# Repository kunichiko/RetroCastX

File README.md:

# RetroCastX

レトロPC(X68000 / PC-98 など)のアナログRGB信号を、フレームバッファレスで PC/Mac に伝送・表示するプロジェクト。

```
Retro PC ──アナログRGB──▶ ADC(TVP7002) ──24bit+PCLK──▶ FPGA(ECP5) ──UDP/GbE──▶ PC/Mac(再構成・表示)
```

## 設計思想

一般的なアップスキャンコンバータは変換器内でフレームバッファを構築し標準的なHDMI信号に整形するため、
機種固有のタイミング情報が失われ、遅延・モード切替時のブラックアウト・価格の問題が生じる。

RetroCastX は「変換器は馬鹿に徹し、知性はPC側に置く」:

- ADC でドットクロックを再生してサンプリングした**生のピクセルデータを、タイミング情報ごと**
  「1パケット≒1ライン」の UDP で送出する(FPGA はラインFIFO程度しか持たない)
- フレームの再構成・スケーリング・表示は PC/Mac 側で行う

これにより:

- **生タイミング保存**: VRR対応モニタなら 55.46Hz(X68000)等の非標準リフレッシュをそのまま表示可能
- **モード切替の無切断追従**: ゲーム中の解像度切替もヘッダ通知で追従
- **真のロスレス**: 8bit で取得し PC 側でパレット吸着(X68000 は本来 RGB 各5bit)
- **低遅延**: サブフレーム(ライン単位)伝送
- **安価**: フレームバッファ用メモリも高度な画像処理も変換器側に不要

## リポジトリ構成

```
docs/
  protocol-v0.md    伝送プロトコル仕様 v0(ドラフト)
  research/         部品・ボード調査レポート
gateware/           FPGA側(LiteX / Colorlight i5)※sim検証済み、実機未検証
hardware/           ADCフロントエンド基板(Atopile、HAT形式)
host/python/        PC側リファレンス実装(送信シミュレータ・受信・検証)
client/             ビューアアプリ(Rust + eframe/egui、Mac/Win/Linux)
client/devsim/      ダミーデバイス(ボードの代役。持っていない機種の信号で Viewer を試す)
```

## クイックスタート(ハードウェア不要)

送信シミュレータと受信器をループバックで動かす:

```sh
cd host/python
python3 -m retrocastx.tests.test_loopback   # プロトコルのE2E検証
python3 -m retrocastx.tests.test_videoin    # コンポジットの波形解析(合成波形で検証)
python3 -m retrocastx.tests.test_ntsc       # NTSC復調(合成6色で真値と照合)
python3 -m retrocastx.sender_sim &          # テストパターンをUDP送出
python3 -m retrocastx.receiver --dump out   # 受信して out/frame_NNNN.ppm に保存
```

## ハードウェア(フェーズ1〜2 想定)

| 役割 | 部品 | 備考 |
|---|---|---|
| FPGAボード | Colorlight i5 + 拡張基板 | ECP5-25F、GbE PHY ×2、SODIMM I/O 直結 |
| ADC | TI TVP7002 | OSSC と同一。15/24/31kHz 実証済み。ブレークアウト自作 |
| 参考回路 | [marqs85/ossc_pcb](https://github.com/marqs85/ossc_pcb) | アナログ入力段・TVP7002 周辺 |

調査の詳細は `docs/research/2026-07-25-hardware-survey.md` を参照。

## ステータス

- [x] 構想・部品調査
- [x] プロトコル v0 ドラフト(映像 LINE/MODE + 音声 AUDIO + 発見/購読 + CONFIG)
- [x] PC側リファレンス実装(シミュレータ + 受信器)
- [x] LiteX ゲートウェア step2(テストパターン送出+購読) — sim検証・ビットストリーム生成済み
- [x] TVP7002 ブレークアウト設計(音声3系統・ArgusX制御含む、電気設計検証まで)
- [x] ビューアアプリ雛形(Rust + eframe、sender_sim相手にE2E確認済み)
- [ ] ゲートウェア実機動作(ボード入手待ち)
- [ ] 基板発注(atopile部品API復旧後にフットプリント紐付け)
- [ ] 音声キャプチャ(gateware step4)・音声再生(client)
- [ ] 実機キャプチャ(X68000 / PC-98)

## ライセンス

ディレクトリごとに異なります。

| 対象 | ライセンス |
|---|---|
| `gateware/` `client/` `host/` | [Apache License 2.0](LICENSE) |
| `hardware/` | [CERN-OHL-S-2.0](hardware/LICENSE)(強い相互性のオープンハードウェアライセンス) |
| `docs/` | [CC BY-SA 4.0](docs/LICENSE) |

`hardware/` の CERN-OHL-S-2.0 は、**この設計を元に製品を作って頒布・販売する場合、
改変を含む設計一式(Complete Source)を公開し、製品または同梱文書に入手先を明記する**
ことを求めます。個人が自分用に作る分にはこの義務は発生しません。

ライセンスの対象外となるファイル(部品メーカーのデータシート、ベンダー由来の
KiCad シンボル・フットプリント等)については [NOTICE](NOTICE) を参照してください。

### 商標

**"RetroCast X"**(正式名称)および **"RetroCastX"**(ファイル名・識別子・
ハッシュタグ等で用いる短縮形)の名称、ロゴ、アイコン、基板シルク上のブランド
表記は、上記いずれのライセンスの許諾範囲にも含まれません
(Apache License 2.0 第6条)。空白の有無・大文字小文字の違いを問いません。

フォークや派生ハードウェアを頒布する場合は、別の名称を用いてください。

### ハードウェアの製造を検討されている方へ

本設計に基づくハードウェアの製造・頒布を計画されている場合、事前にご一報
いただけると嬉しいです。**ライセンス上の義務ではありません**が、既知の問題や
実装上の落とし穴を共有できますし、改善を上流に取り込める場合もあります。

## コントリビューション

歓迎します。手順と DCO(Signed-off-by)については [CONTRIBUTING.md](CONTRIBUTING.md)
を参照してください。特に**手元の実機での動作報告**が助かります。

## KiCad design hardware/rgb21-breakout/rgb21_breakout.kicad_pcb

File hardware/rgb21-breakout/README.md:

# RGB21 → ミニDIN8 変換基板

市販のミニDIN8ケーブルを半分に切り、切った側に **RGB21(JP21)のメスコネクタ**を
付けて、ゲーム機の RGB21 ケーブルを RetroCastX の第2映像入力(J13、FRAMEMEISTER 互換の
ミニDIN8)に挿せるようにする。この基板は RGB21 コネクタのシェル(カバー)の中に収める
三角形の中継基板。

```
ゲーム機 ── RGB21ケーブル(オス) ─┐
                                  ▼
             ┌─ RGB21 メス(J1) ── 基板の端を2列の半田端子で挟む
  シェルの中 │        │ 素通し(部品なし)
             ├─ 芯線パッド(J2) ─ 表4個・裏4個 ─┬ ミニDIN8ケーブル ── RetroCastX J13
             └─ シールドのパッド(J3) ─────────┘
                  └ タイラップ用スロット(H1)でケーブルを基板に縛る
```

回路は**素通しの配線だけ**。分圧・終端・同期分離は入れない。FRAMEMEISTER 付属の
「ミニDIN8→RGB21」ケーブルも素通しで(2026-09-21 に分解して確認)、レベル合わせは
RetroCastX 側(75Ω終端・CSYNC の 1/2 分圧)でやる。

## 結線

| 信号 | RGB21(J1) | ミニDIN8(J2) | J2 の面 |
|---|---|---|---|
| R | 15 | 8 | 裏 |
| G | 19 | 7 | 裏 |
| B | 20 | 6 | 裏 |
| 同期(CSYNC) | 9(コンポジット入力) | 3 | 表 |
| 音声 L | 1 | 2 | 表 |
| 音声 R | 5 | 1 | 表 |
| GND | 3, 4, 7, 8, 13, 14, 17, 18 | 4 | 表 |
| シェル(FG) | 21 | シールド(編組) | J3(スルーホール) |
| 使わない | 2, 6, 10(モニタの出力), 11 AV制御, 12 Ym, 16 Ys | 5(パッドはあるがどこにも繋がない) | 裏 |

- RGB21 のピン名はモニタ(受け側)から見た名前。ゲーム機のケーブルを挿すので、
  ゲーム機の出力は「入力」のピンに来る。出典: ja.wikipedia「RGB21ピン」と
  retrogamingcables の JP21 表(R/G/B/同期/音声で一致)。
- 同期は 9番。RGB21 には同期専用ピンが無く、ゲーム機は CSYNC かコンポジット映像を
  ここに出す。
- ミニDIN8 は FRAMEMEISTER RGB IN と同じ並び(`hardware/adc-frontend` の
  `MiniDin8Rgb` の docstring)。5番は使わないが、芯線の端を留めるためのパッド(どこにも繋がない)がある。
- FG(シェル/シールド)は GND と分けてある。RetroCastX 側で J13 のシェルが GND に
  繋がるので、ケーブルを挿せば同電位になる。
- **J2 はピン番号順に並べてある**: 表が 1 2 3 4(表から見て左→右)、裏が 5 6 7 8 で、
  1 の真裏が 5、2 の真裏が 6 … になる。この基板の目的は芯線を付けやすくすることなので、
  基板上の配線が交差しても番号順を優先した。シルクにはパッドの脇にピン番号、その外に
  信号名を書いてある。表・裏は J2 のフットプリントから見た面で、PCB 上で J2 を裏返して
  置けば入れ替わる。
- **シールド(FG)は J3 に分けた**: より合わせた編組は太く、芯線のパッドと並べると
  隣に触れやすいので、離して置ける別部品のスルーホールパッド(直径 3.5mm・穴 1.8mm)にした。
  表裏どちらからでも付けられ、穴に通せば抜けにくい。
- **芯線の色はケーブルごとに違う。** 半田付けの前に、プラグのピンと芯線の導通を
  テスタで確かめて色を控えること。

## 回路は kinema で書いている

atopile ではなく [kinema](https://github.com/toyoshim-i/kinema) を試している。
Verilog の構造記述のサブセットで部品と接続を書き、KiCad のネットリストを生成する。
**回路図(.kicad_sch)は無い。** 正本は `src/` と `lib/` の `.v`。

| ファイル | 中身 |
|---|---|
| `src/rgb21_breakout.v` | 回路(J1 と J2・J3 の接続) |
| `lib/parts.v` | 部品(ピン番号と電気的な向き) |
| `rgb21_breakout.pretty/` | 自作フットプリント。**`tools/gen_footprints.py` の生成物なので手で直さない** |
| `fp-lib-table` | 上のフットプリントを `rgb21_breakout:` で参照する表 |
| `kinema.toml` | kinema の設定 |
| `rgb21_breakout.kicad_pcb` | 基板。配置・配線はここで手作業 |
| `tools/make_board.py` | PCB を最初の1回だけ作ったスクリプト(PCB があれば何もしない) |

### kinema の入れ方

2026-11-23 時点で GitHub Releases の最新バイナリ(v0.5.0)はソースの版(0.6.4)より
古いので、ソースから入れた(Rust が要る):

```sh
git clone https://github.com/toyoshim-i/kinema
cargo install --path kinema/crates/kinema-cli
```

### 回路を変えたとき

このフォルダで:

```sh
kinema fmt src/*.v lib/*.v           # 正規形に整形(check の fmt 段が要求する)
kinema check --stage lint            # 文法・接続・フットプリントの有無・パッド数
kinema netlist -o build/rgb21_breakout.net
```

そのあと PCB エディタで **File → Import → Netlist…** から `build/rgb21_breakout.net`
を読み込む(**「タイムスタンプで照合」**を選ぶ)。部品の同一性は `.v` の
`(* id = "..." *)` から作られる UUID で決まるので、参照番号を変えても配置は残る。
`id` を変えると別部品扱いになり、配置が消えるので変えないこと。

配線を終えたら照合:

```sh
kinema check --stage equiv           # PCB のパッドとネットが回路と一致するか
```

R と G を入れ替えた PCB で `net-partition-mismatch` が出ることを確かめてある。

### kinema 0.6.4 で踏んだこと

- **`fp-lib-table` を相対パスで指定すると自作フットプリントが見つからない。**
  表の置き場所を `${KIPRJMOD}` にするとき親ディレクトリが空文字になり、
  `/rgb21_breakout.pretty` を探しに行って `footprint-missing` になる。自動検出でも
  同じ。`kinema.toml` で `fp_lib_table = "./fp-lib-table"` と `./` 付きで書いて回避した。
- 全ピンを `passive` にすると全ネットに `undriven-net` の警告が出る。J1 の使う信号は
  `output`、J2 の信号は `input`、J2 の GND/シールドは `power_out` にしてある。
- **`check --stage equiv` は、どこにも繋がないパッドが PCB に無くても通る。** ネットのある
  パッドしか比べないため。J2 に5番(NC)のパッドを足したとき、古いフットプリントのままの
  PCB でも照合が通った。パッドの数は `--stage lint` がライブラリ側でしか見ないので、
  フットプリントを変えたら PCB 側の更新は目で確かめる。
- タイラップのスロット(H1)は回路に無い部品なので、フットプリントに
  `(attr board_only)` を付けて照合から外している。

## 残りの作業

1. **寸法を実測して `tools/gen_footprints.py` の ★ の値を直す**:
   - ~~RGB21 端子のピッチ~~ → SCART の仕様で同じ列 3.81mm(列どうしは半ピッチ 1.905mm ずれて
     交互に並ぶ)に決めた。全幅はピン1〜21の中心で 38.1mm
   - 端子の板幅と基板に乗る長さ(パッド 2.0 × 4.0mm で仮置き)
   - 2列の間隔が基板の厚み(1.6mm)で挟めるか。合わなければ板厚を変える(1.2 / 2.0mm など)
   - どちらの列が奇数ピン(1〜19 と 21=シェル)か。今は奇数を裏、偶数を表にしてある
   - タイラップの幅・厚みとケーブルの外径(スロット 1.3 × 3.2mm、中心間 9mm)
   - より合わせたシールドの太さ(J3 の穴 1.8mm、パッド 3.5mm)

   直したら `python3 tools/gen_footprints.py` を実行し、PCB エディタで
   Tools → Update Footprints from Library。
2. **外形と配線は一通り済んだ**(2026-11-24、DRC 違反 0・未配線 0、`kinema check --stage equiv` 通過)。
   ただし上の ★ の寸法は仮置きのままなので、実測で値が変わったら外形・配置・配線を見直す。
   外形はシェル内の三角形に合わせ、J1 の原点(Fab 層の破線 "board edge")が差し込む辺。

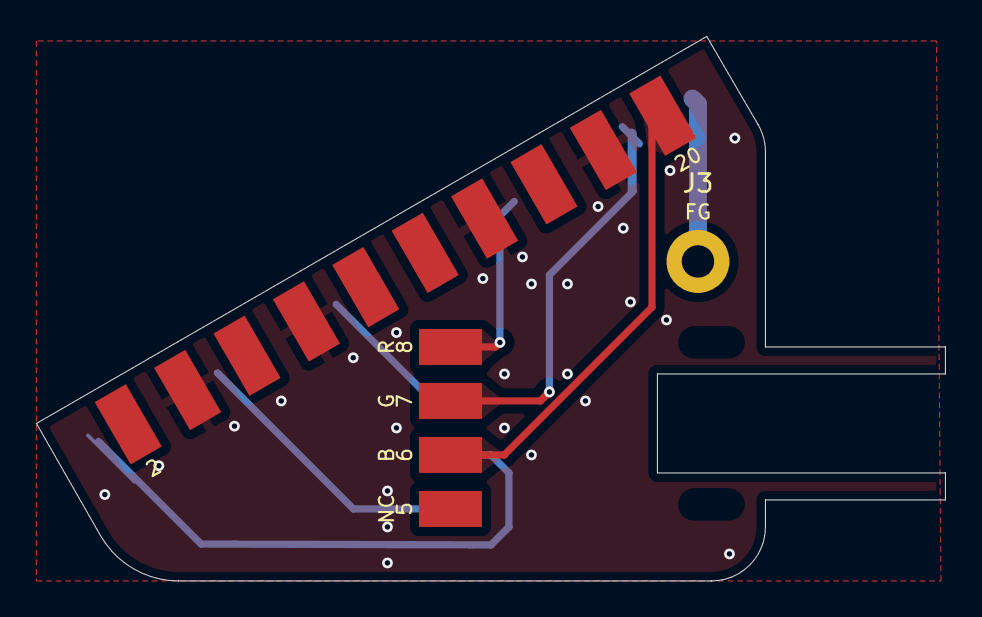
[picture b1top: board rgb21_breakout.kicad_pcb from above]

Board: 2 copper layers, 50.5 x 30.2 mm, 4 parts (1 on the bottom side), 8 nets.

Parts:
H1: CableTie_Slots
J1: RGB21_Female; RGB21_CardEdge
J2: MiniDin8_Cable; MiniDin8_WirePads
J3: ShieldWirePad; FG_WirePad

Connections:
AUDIO_L: J1.1, J2.2
AUDIO_R: J1.5, J2.1
B: J1.20, J2.6
CSYNC: J1.9, J2.3
FG: J1.21, J3.1
G: J1.19, J2.7
GND: J1.3, J1.4, J1.7, J1.8, J1.13, J1.14, J1.17, J1.18, J2.4
R: J1.15, J2.8

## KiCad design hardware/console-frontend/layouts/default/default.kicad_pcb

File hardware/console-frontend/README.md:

# RetroCastX 小亀基板(コンソール入力基板) v1.0

家庭用ゲーム機向けの入力端子を引き受けて、**0.5mmピッチ20芯FFC(10cm)**で
メイン基板(`hardware/adc-frontend`)へ渡すサブ基板。外形はメイン基板と同じ
**10cm × 10cm**、取付穴は M3 ×5(メイン基板の H1-H5 と同じ位置にしてスペーサで重ねられる)。

> **発注済みの v1.0.1 には手作業の改修が2つ要る**(映像の結合コンデンサ C6〜C9 と、
> 音声の分圧)。図つきの手順は [docs/rework-v1.0.1.md](docs/rework-v1.0.1.md)。

```
  S端子(ミニDIN4) ─┬─ESD─ 75Ω ─ 10µ ──┬(bias 1.65V)─┐
                   │                                  ├ SPDT ch1 ─ FFC 9 ─→ GIN_1 / SOGIN_1
  コンポジット(黄) ─┴─ESD─ 75Ω ─ 10µ ──┘              │   (ESD: D2=CVBS/音声L/R
                                                       (選択 = FFC 15 = FPGA GPIO)
  S端子C ───────────ESD─ 75Ω ─ 10µ ───┬──────────────┤    D3=S端子Y/C・Pr/Pb)
  コンポーネントPr(赤)─ESD─ 75Ω ─ 10µ ─┘              └ SPDT ch2 ─ FFC 7 ─→ RIN_1

  コンポーネントPb(青)─ESD────────────────────────────── FFC 5 ─→ BIN_1(終端はメイン基板側)
  音声L(灰/黒) ─ESD─ 10k ─┬─────────────────────────  FFC 1 ─→ PCM1808 #3
                          10k→GND(×0.46。PCM1808 のフルスケール 3Vpp に 2Vrms を収める)
  音声R(赤)   ─ESD─ 10k ─┬─────────────────────────  FFC 3 ─→ PCM1808 #3
                          10k→GND
  シリアルLED ×4 ←── FFC 11(データ)/ 17・18(+3.3V 直結)
```

Y/C分離も復調もこの基板ではやらない。メイン基板の TVP7002 で 8fsc サンプリング
して、Viewer(PC側)でデコードする(`docs/composite-video-plan.md`)。

## 音声のハムはケーブルで決まる(この基板では対処しない)

PS2 のサードパーティ製コンポーネントケーブルで、音声に **59.94Hz とその倍音のハム**
(−58dBFS)が乗った(2026-11-08)。Y を抜くと消え、白い画面ほど大きい。
映像の 75Ω 終端の電流はケーブルの GND を通ってゲーム機へ戻るので、その電圧降下が
ゲーム機と小亀基板の GND の間にでき、ゲーム機の GND 基準で出ている音声に乗る。

テスターで測ると、このケーブルは映像(緑)と音声の GND が **RCA 側の近くで合流し、
マルチ端子まで約1.75Ωを共用**していた(緑⇔ピン 2Ω、音声⇔ピン 2Ω、緑⇔音声 0.5Ω)。
共用区間の電圧降下は受け側で差動にしても消せないので、差動アンプ案は採らなかった。
純正のコンポジット(GND 間 5Ω)/S端子(絶縁)ケーブルではノイズは出ない。
**対策はケーブルを替えること。**

(メイン基板と共通)

メイン基板(J15)側の番号で書く。**小亀基板(J1)は逆順(n ↔ 21-n)**。

| pin | 信号 | pin | 信号 |
|---|---|---|---|
| 1 | 音声L | 11 | LED_DATA |
| 2 | GND | 12 | GND |
| 3 | 音声R | 13 | GPIO2(予備) |
| 4 | GND | 14 | GND |
| 5 | Pb(スイッチを通らない) | 15 | GPIO1(スイッチ選択) |
| 6 | GND | 16 | GND |
| 7 | C / Pr(スイッチ出口) | 17 | +3.3V |
| 8 | GND | 18 | +3.3V |
| 9 | Y / CVBS(スイッチ出口) | 19 | +5V |
| 10 | GND | 20 | +5V |

**信号は全部が両隣にGNDを持ち、電源は2本ずつ**(2026-09-22 に16芯から20芯へ)。
16芯のときは制御3本(LED_DATA/GPIO2/GPIO1)が並んでいて、800kHzのLEDデータが
隣のGPIOと並走していた。電源を2本にしたのは往復抵抗を半分にするため。

★**ケーブルの向き(type A / type D)は発注前に確認すること。** FFCは両端の接点が
同じ面か反対面かで「n番 ↔ n番」と「n番 ↔ 21-n番」が入れ替わる。**このネットリストは
type A(同面接点)+ 2枚を同一平面・開口部を向かい合わせ、を前提に小亀側を
逆順(n ↔ 21-n)で定義してある**(`main.ato` の `FfcMain20` docstring が正典)。
2枚の基板の向きを決めたら紙に描いて種別を選び、**通電前にテスターで
pin1↔pin1 を当たること**。1ピンずれると +5V が GPIO に当たる。

## 入力の切り替え(TS5A23159 / 1本の選択線)

真理値表(データシート SCDS201H Table 2: IN=L → NC-COM が ON)。

| GPIO1 (= FFC 15) | FFC 9 (→GIN_1/SOGIN_1) | FFC 7 (→RIN_1) | FFC 5 (→BIN_1) | 使える入力 |
|---|---|---|---|---|
| **L(既定・10kプルダウン)** | CVBS(黄) | Pr(赤) | Pb(青) | コンポジット / **YPbPrコンポーネント** |
| H | S端子 Y | S端子 C | (Pb) | S端子 |

- **既定をコンポジットにした理由**: ゲートウェアがこのGPIOを駆動しない状態でも
  「黄色いケーブルを挿しただけで映る」ようにするため。S端子とコンポーネントは
  Viewer で明示的に選ぶ操作を伴うので、そのときに H へ駆動される。
- **同期(SOGIN_1)はスイッチの出口から分岐している**ので、映像と同期が必ず
  一緒に切り替わる。人が触る物理スイッチだと「設定はコンポジットなのにスイッチは
  S端子側」という食い違いを作れてしまう(`docs/TODO.md` 10-5)。
- break-before-make なので、切り替えの瞬間に2つのソースが繋がることはない。

## 75Ω終端と中点バイアス(この基板の設計の要点)

**終端はこの基板のジャック側に置く**。メイン基板の `VideoInputChannel` が持つ
75Ω(`r_term`)は、**この基板で終端するチャンネル(Y/C)では実装しない**。
両方に入れると合計37.5Ωになり振幅が半分になる。

終端の直後に 10µF で直流を切り、10kΩ で 1.65V(VCC/2)へ持ち上げてから
スイッチに入れている。理由は**スイッチの信号範囲が GND〜VCC** だから:

★**結合は 10µF(時定数 0.1 秒)。v1.0 初版は 100nF(1ms)だった。** 1ms でも
1ライン(63.5µs)より十分長いつもりだったが、明るい区間の後ろで黒が 7〜9 コード
沈んだ(コンポーネントで実測、2026-11-08。手持ちの 0603 10µF に張り替えて解消)。
S端子の C(C8)は低域を持たないので 100nF でも困らないが、部品を揃えて 4つとも 10µF にした。
同じ理由でメイン基板の SOG 結合(C51)は 1nF にしてある(データシートの指定どおり)。
```
出力にコンデンサが入っている機種(AC結合)を 75Ω でGNDへ終端すると、
波形の平均が0Vになるので同期先端が負に潜る
    暗い絵(平均0.35V)  同期先端 ≈ -0.35V
    白い絵(平均0.85V)  同期先端 ≈ -0.85V   ← 絶対最大 -0.5V を超える
潜る量が絵の明るさで動くので、スイッチの保護ダイオードが同期先端だけを食う。
同期先端は SOG スライサが見ている場所なので、明るい絵のときだけ同期が乱れる。
```

v0.9.0(2x4ヘッダ)は同じ 75Ω→100nF の並びだったが、終端ノードに能動素子が
無かったので問題にならなかった。スイッチを入れる v1.0 では効いてくる。

Pb だけはスイッチを通らないので直流結合のまま渡し、終端もメイン基板側
(`ch_b1` の 75Ω)に任せている。

## 部品(LCSC)

| 部品 | 型番 | LCSC | 備考 |
|---|---|---|---|
| ミニDIN4(S端子) | **マル信 MJ-373/4B** | — (手実装) | 千石/マルツ/モモハラ。3=Y / 4=C / 1,2=GND / スロット3本=シェル |
| RCA ×5 | **RCA-105**(色違い) | — (手実装) | AliExpress等。黄/白/赤/黒/青が同寸法で揃う。**2端子・両方とも軸線上** |
| FFCコネクタ | HDGC 0.5K-1.5-**20**PWB | C2919559 | 下接点・フリップロック・右アングル |
| アナログスイッチ | TI TS5A23159DGSR | C42751 | 2ch SPDT, Ron 1Ω, break-before-make |
| ESD ×2 | onsemi NZQA6V8AXV5T1G | C895163 | メイン基板と同じ。旧 EMZT6.8ET2R(C510333)が JLC 在庫切れのため v1.0 発注前に差し替え。ピン互換(SOT-553 = EMD5 同寸、リード2が共通アノード)で、フットプリントは旧品の5パッド版をそのまま使う |
| シリアルLED ×4 | Worldsemi WS2812B-2020-V6 | C52917434 | 3.3V直結、LED1→LED4 の直列(v1.0 発注前に2個から4個へ)。**MSL 5a(JLCの焼成料金がかかる)**。D1(旧 1N4148W)は欠番 |

ミニDIN4はLCSCに無いので**フットプリントをメーカー図面から自作**した
(`parts/_mech/MJ373_4B.kicad_mod`。φ1.2×4 + スロット2.8×0.8×3、原点=嵌合面)。
メイン基板のミニDIN8(マル信 MJ-373/8B)と同じハウジング/ランド枠。

RCAは**フットプリントをメーカー図面から自作**した(`parts/_mech/RCA105.kicad_mod`)。
ランドは **2端子だけで、両方ともコネクタの軸線上**:

    pad1  スロット 軸方向 1.50 × 横 2.30  @ 嵌合面から 4.80  → シェル(GND)
    pad2  スロット 軸方向 2.30 × 横 1.00  @ 嵌合面から 8.30  → 中心導体(信号)

図面の「2.30x1.50」「1.00x2.30」は軸が縦の図での横×縦。v1.0.0 は軸方向と読み違えて
両スロットが 90° 回っていた(v1.0.1 で修正。pad1 の前足は軸と直角の板、pad2 の後ろ足は軸方向の板)。

★**極性は現物で導通確認すること。** 2端子しかないので取り違えると映像をGNDへ短絡する
(「筒の外側 ↔ pad1」「中心の穴 ↔ pad2」を当てれば10秒)。
★**同じ RCA-105 でも出品元で寸法が違うことがある**ので、4.80/8.30 とスロット寸法を実測してから発注する。
★外形と並べ方(枠10.0mm・筒がφ8.3で9.3mm張り出す・ピッチは12.5mm)は
`docs/layout-guidelines.md` の1章にまとめた。

レイアウトの指示は `docs/layout-guidelines.md`(外形・コネクタ形状・配置・配線ルール)。

## ビルド

```
ato build                               # ネットリスト/PCB/BOM を生成
```

部品の取り込み(atopileの部品APIが落ちているときのオフライン手順)は
メイン基板と同じ `tools/ingest_parts.py`:

```
~/.local/share/uv/tools/atopile/bin/python tools/ingest_parts.py C2939342 ...
```

★**ESDアレイのフットプリント(ROHM_EMZT6_8ET2R。現行の NZQA6V8AXV5T1G もこれを使う)を取り込み直したら `tools/fix_esd_land.py` を必ず走らせる**
(取り込み時のフットプリントはリードの無い裸パッドを含む6パッド版で、パッド幅も
0.28mmしかない)。いまリポジトリに入っているのはメイン基板で修正した5パッド版。

## 発注前チェックリスト

1. **FFCの向き**: type A(同面接点)+ 対向配置の前提で小亀側を逆順(n↔21-n)にしてある。
   紙に描いて確認し、通電前に pin1↔pin1 を導通確認
2. **ミニDIN4のピン**: 現物で「3番がプラグの輝度ピン」を導通確認(図面の
   PCB穴図のパッド番号=ミニDIN4の標準ピン番号として扱っている)
3. **RCA-105 の極性とランド**: pad1=GND / pad2=信号 を導通確認し、4.80/8.30 を実測
4. **メイン基板側の 75Ω**: `ch_y` / `ch_c` の `r_term` を実装しない指定になっているか
   (v1.0 の main.ato では `VideoInputChannelNoTerm` を使う。未対応なら手で外す)
5. 取付穴の位置をメイン基板と合わせる(M3 ×4)

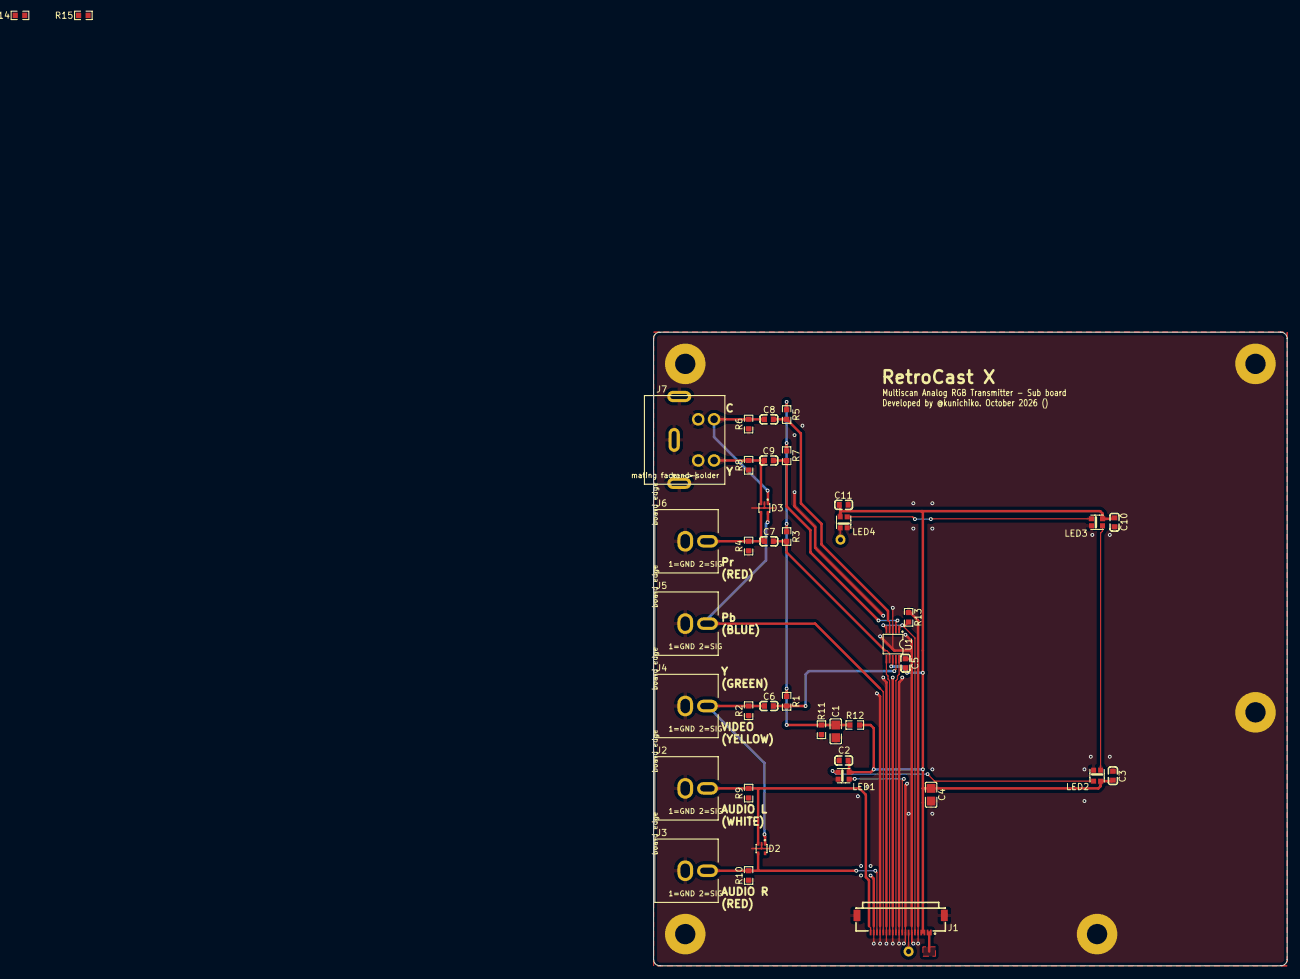
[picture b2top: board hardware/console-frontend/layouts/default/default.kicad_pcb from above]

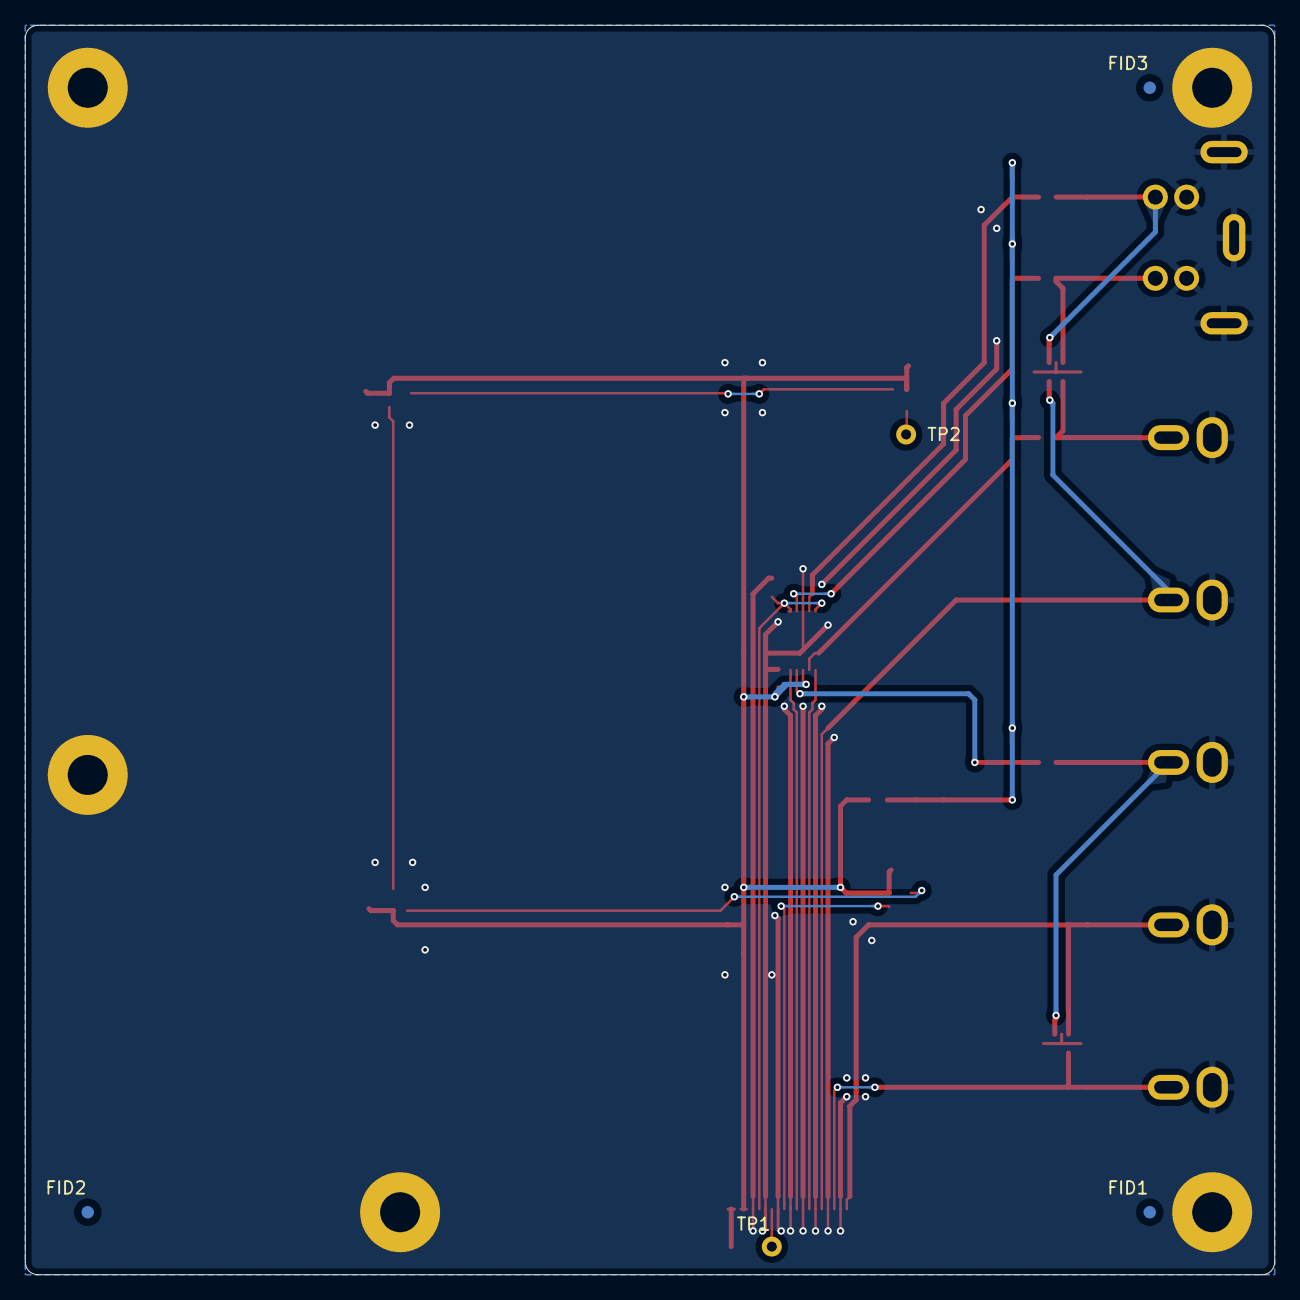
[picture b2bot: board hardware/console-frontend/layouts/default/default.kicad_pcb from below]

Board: 2 copper layers, 100.0 x 100.0 mm, 50 parts (9 on the bottom side), 26 nets.

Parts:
C1, C4: 10µF ±10%; C0805
C2, C3, C5, C10, C11: 100nF ±10%; C0603
C6, C7, C8, C9: 10µF ±10%; C0603
D2, D3: EMT6_L1.6-W1.2-P0.50-LS1.6-BL
FID1, FID2, FID3: Fiducial_1mm_Mask2mm
H1, H2, H3, H4, H5: MountingHole_3.2mm_M3_Pad
J1: FPC-SMD_20P-P0.50_HDGC_0.5K-1.5-20PWB
J2, J3, J4, J5, J6: RCA105
J7: MJ373_4B
LED1, LED2, LED3, LED4: LED-SMD_4P-L2.2-W2.0-P1.00_WS2815C-2020-4P
R1, R3, R5, R7, R9, R10, R11, R12, R13, R14, R15: 10kΩ ±1%; R0603
R2, R4, R6, R8: 75Ω ±1%; R0603
TP1, TP2: TestPoint_TH1
U1: VSSOP-10_L3.0-W3.0-P0.50-LS4.9-BL

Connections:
aud_l_in: D2.3, J2.2, R14.1
aud_l_out: J1.20, R9.1, R14.2
aud_r_in: D2.4, J3.2, R15.1
aud_r_out: J1.18, R10.1, R15.2
c_out: J1.14, U1.6
cvbs_ac: C6.2, R1.1, U1.9
cvbs_in: C6.1, D2.1, J4.2, R2.1
gnd: C1.2, C2.2, C3.2, C4.2, C5.2, C10.2, C11.2, D2.2, D3.2, H1.1, H2.1, H3.1, H4.1, H5.1, J1.5, J1.7, J1.9, J1.11, J1.13, J1.15, J1.17, J1.19, J1.21, J1.22, J2.1, J3.1, J4.1, J5.1, J6.1, J7.1, J7.2, J7.5, J7.6, J7.7, LED1.2, LED2.2, LED3.2, LED4.2, R2.2, R4.2, R6.2, R8.2, R9.2, R10.2, R11.2, R13.2, U1.3
gpio2: J1.8, TP1.1
led1_dout: LED1.1, LED2.3
led2_dout: LED2.1, LED3.3
led3_dout: LED3.1, LED4.3
led4_dout: LED4.1, TP2.1
led_din: J1.10, LED1.3
p3v3: C2.1, C3.1, C4.1, C5.1, C10.1, C11.1, J1.3, J1.4, LED1.4, LED2.4, LED3.4, LED4.4, R12.1, U1.8
p5v: J1.1, J1.2
pb_out: D3.5, J1.16, J5.2
pr_ac: C7.2, R3.1, U1.7
pr_in: C7.1, D3.4, J6.2, R4.1
sv_c_ac: C8.2, R5.1, U1.4
sv_c_in: C8.1, D3.1, J7.4, R6.1
sv_y_ac: C9.2, R7.1, U1.2
sv_y_in: C9.1, D3.3, J7.3, R8.1
sw_sel: J1.6, R13.1, U1.1, U1.5
vbias_1v65: C1.1, R1.2, R3.2, R5.2, R7.2, R11.1, R12.2
y_out: J1.12, U1.10

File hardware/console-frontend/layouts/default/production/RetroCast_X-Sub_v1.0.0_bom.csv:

Designator,Footprint,Quantity,Value,LCSC Part #
"C1, C4",C0805,2,10µF ±10%,C15850
"C10, C11, C2, C3, C5, C6, C7, C8, C9",C0603,9,100nF ±10%,C14663
"D2, D3",EMT6_L1.6-W1.2-P0.50-LS1.6-BL,2,,C895163
J1,FPC-SMD_20P-P0.50_HDGC_0.5K-1.5-20PWB,1,,C2919559
"J2, J3, J4, J5, J6",RCA105,5,,
J7,MJ373_4B,1,,
"LED1, LED2, LED3, LED4",LED-SMD_4P-L2.2-W2.0-P1.00_WS2815C-2020-4P,4,,C52917434
"R1, R10, R11, R12, R13, R3, R5, R7, R9",R0603,9,10kΩ ±1%,C25804
"R2, R4, R6, R8",R0603,4,75Ω ±1%,C4275
"TP1, TP2",TestPoint_TH1,2,,
U1,VSSOP-10_L3.0-W3.0-P0.50-LS4.9-BL,1,,C42751

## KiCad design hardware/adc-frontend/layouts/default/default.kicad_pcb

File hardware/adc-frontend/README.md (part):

# RetroCastX ADC フロントエンド(TVP7002 ブレークアウト)

レトロPCのアナログRGB(VGA HD-15経由)を TI TVP7002 でデジタル化し、
24bitパラレル + DATACLK/HSOUT/VSOUT/SOGOUT を Colorlight i5 EXTボードへ渡す
**HAT基板**(EXTのP1/P2/P4に直接スタック)。GbE MagJack・**音声入力4系統**・
ArgusX制御コネクタ搭載。回路は `main.ato`(Atopile)。

## v1.0 の変更点(v0.9.0 → v1.0)

v0.9.0(2026-08-19 発注、実機動作確認済み)からの差分。**電気的に効く変更**と
**部品・コネクタの入れ替え**を分けて書く。

### 入力コネクタ

| 端子 | v0.9.0 | v1.0 |
|---|---|---|
| アナログRGB | D-SUB15(2列DA-15, X68000式) | 変更なし |
| 第2映像入力 | J4: 2×5 ボックスヘッダ(要自作ケーブル) | **J13: ミニDIN8(FRAMEMEISTER互換)** |
| 第2入力のTTL同期 | 同ヘッダの9/10ピン | **J14: 1×3 ヘッダ(HSYNC/VSYNC/GND)** |
| S端子/コンポジット | J5: 2×4 ボックスヘッダ | **J15: 20芯FFC → 小亀基板**(`hardware/console-frontend`)。並びは `音声L/GND/音声R/GND/Pb/GND/C/GND/Y/GND/LED/GND/GPIO2/GND/GPIO1/GND/+3.3V/+3.3V/+5V/+5V`(全信号がGNDに隣接、電源は2本ずつ) |
| 光デジタル(S/PDIF) | J8: PLR135/**T** | J8: PLR135/**T10**(ランドが小さい) |
| デジタルRGB | J6: 1.25mm 単列8極(SMD) | **J6: 2×5 ボックスヘッダ(ストレート)**(XFCN BH254V-10P, C492442)。一般的な10芯フラットケーブルが使える。位置も別エッジへ移動 |
| USB-C | J2 | 変更なし |

### 電気的な変更

- **同期入力にプルアップ 10kΩ を追加**(R47-R50)。D-SUB と 1x3 ヘッダの
  HSYNC/VSYNC。未接続時にシュミット入力が浮いて自己発振し、捕捉側の `raw_ok` が
  誤って立つ不具合(`docs/TODO.md` 10-5b、実機 2026-09-06)の根本対策。
  **プルダウンではなくプルアップ**(レトロ機のTTL同期は負極性=アイドルHigh。
  オープンコレクタ出力の機種にも対応できる)
- **PCM1808 を2個 → 3個**。映像系統ごとに独立させ、受動加算の 1.5kΩ×4 を廃止
- **BIN_1 を実入力に昇格**(小亀基板の Pb / 予備線)。未使用終端の 10nF を撤去し、
  他のチャンネルと同じ前段(75Ω/100nF/220Ω/33pF)を付けた
- **S/PDIF受信の電源にフェライト+10µFを追加**(FB4/C96)。データシートの応用回路が
  47µH+0.1µF を要求しているのに v0.9.0 は 0.1µF だけだった
- **ネジ穴 M2.6 → M3**(穴2.8→3.2mm、パッド5.6→6.4mm)。ねじとスペーサの入手性
- ミニDIN8 の R/G/B/CSYNC に ESD を追加(v0.9.0 の 2x5 ヘッダ経路には無かった)
- **JTAGデバッグ端子(J3, 1×6ヘッダ)を削除**。「外部JTAG器を繋げるように」という保険
  だったが、**FPGAのJTAGへ届く経路はモジュール底面のパッド = ポゴピンしか無い**ので、
  ポゴピンが届かない場合の保険にはならない(CH347Fが壊れた場合にしか効かない)。
  J3 は欠番のまま(`tools/lock_designators.py` が番号の再利用を防ぐ)
- **ステータスLED(LED1)を WS2812B-2020-V6(C52917434)の 3.3V 直結に変更**。
  V6 は VDD 3.3〜5.3V・VIH 0.55×VDD なので、5V + 1N4148W の降圧が不要になった
  (D7 は欠番)。**MSL 5a のため JLCPCB の焼成料金がかかる**(承知のうえで採用)
- **ESDアレイを onsemi NZQA6V8AXV5T1G(C895163)に差し替え**。EMZT6.8ET2R(C510333)が
  JLCPCB で在庫 0 になったため。SOT-553 は EMD5 と同寸でリード番号も同じ(リード2 = 共通
  アノード)なので、**フットプリントと配線はそのまま**。VBR は同じ 6.47〜7.14V、Ct は
  7pF → 12pF typ に増えるが、映像(37.5Ω 系で極 約350MHz)にも TTL にも実害は無い
- **TVP7002 を PZPR(C527698、テープ&リール品)に変更**。中身とフットプリントは PZP と同じ
- **MAC EEPROM を SOT-23-6 の 24AA025E48T-I/OT(C129895)に変更**。SOIC 版は JLC 在庫が
  足りなかった(-I/SN 6個 / -E/SN 32個、1枚に2個使う)。A2 と WP のピンが無いが、A2 は内部で 0、
  WP は元々 GND 固定(書込み許可)なので 0x50 / 0x51 の割当も動作も同じ
- **手ハンダ部品(J7-J10, J13, J14, PG1-PG4, TP1, TP2)を BOM から除外**(フットプリントに
  exclude_from_bom)。JLC の BOM で「型番なし」の警告が出ないようにするため
- **SOG シャントの未実装 33pF(C32/C40/C52)を 0402 → 0603 に変更**。必要になったら手ハンダで
  載せるため。専用フットプリント `parts/_mech/C0603_DNP`(DNP・BOM/座標ファイル除外)にした。
  0402 版は BOM に型番なしで残り、JLCPCB が勝手に C162097 を割り当てていた

### ソフト側に必要な追随(v1.0 基板を使うとき)

- 音声ソースが3系統になる(`i2s_dout_dsub` / `i2s_dout_din8` / `i2s_dout_kokame`、
  DOUT は SO-DIMM 141 / 139 / **129**)。AUDIOパケットの source 番号が増える
  → **対応済み**: source 0=D-SUB15(U13) / 1=ミニDIN8(U14) / 2=S/PDIF /
  3=小亀基板(U17)。S/PDIF の 2 を動かさず末尾に足した(`docs/protocol-v0.md`)
- 小亀基板のアナログスイッチ選択線が **SO-DIMM 148(K4)**、予備が150(K5)、
  小亀のシリアルLEDデータが **154(A2)**。プロファイルから駆動する
- ミニDIN8 のプロファイルは **SOGスライス閾値(CONFIG key 0x50)を下げる**
  (規格準拠ケーブルのCSYNCは0.3Vpp → 1/2分圧後0.15Vpp。既定のNTH=11=124mVでは
  振幅の83%を切ってしまう。NTH=7 = 79mV が50%点)

## 次の版への要望: 入力ごとの信号検出(2026-11-09)

Viewer は入力を「端子 × 機種」で選ぶ形になり、端子ボタンに信号の有無を出している。
**選んでいない端子の有無も分かるようにしたい**(電源を入れた機械の端子が光る、
テレビの入力切り替えと同じ体験)。いまの基板では端子ごとに次の差がある:

| 端子 | いまの測り方 | 選んでいないとき |
|---|---|---|
| 入力1 ビデオ(小亀基板 → SOGIN_1) | TVP の HSOUT 周波数(key 0x58)の安定性 | **測れない** |
| 入力2 ミニDIN8(CSYNC → 1/2分圧 → SOGIN_2) | 同上 | **測れない** |
| 入力3 D-SUB15(HSYNC 別線) | 生HSYNC を FPGA が数える(key 0x2A) | 測れる |
| 入力4 デジタルRGB | FPGA が数える(key 0x70) | 測れる |

### なぜいまの基板では無理か(実測 2026-11-09)

TVP7002 の同期スライサは1つで、reg 19h の SOG ビットで SOGIN_1/2/3 のどれか1本を
選ぶ。X68000(HSYNC 別線、0Eh=0x52)を映している間はスライサが空いているので、
**SOG ビットだけ他の入力へ向けて SOGOUT を FPGA で測れば絵を乱さずに見られる**と
考えて試したが、駄目だった:

| 19h の SOG | X68000 側 fH / lines | SOGOUT 最長Low(key 0x61) |
|---|---|---|
| (コンポジット設定、0Eh=0x5B) | 15734 / 262 | **774**(垂直ブロードパルス) |
| _1 コンポジット(信号あり) | 15980 / 521 | 65 |
| _2 ミニDIN8(未接続) | 15980 / 521 | 65 |
| _3 D-SUB 緑 | 15980 / 521 | 65 |

X68000 の同期は乱れなかったが、**HSYNC 別線の設定では SOGOUT に SOGIN の信号が
出てこない**(どこへ向けても同じ値)。手順: `retrocastx.videoin apply x68k` のあと
key 0x69 を 0x2A / 0x6A / 0xAA(R/G/B は _3 のまま SOG だけ _1/_2/_3)へ振り、
それぞれ 3.5 秒待ってから 0x58 / 0x5A / 0x61 を4回読んだ。

### 案: FPGA の差動入力をコンパレータにする(IC を足さない)

入力3・4 と同じく「FPGA がエッジを1秒数える」形に揃える。判定は Viewer 側に
既にある(2回の読みが ±4Hz で一致 = 信号あり)。

★**同期分離 IC(LM1881 系)は使わない。** TVP7002 が同期分離を持っているので
LM1881 を排除できた構成なのに、検出のためだけに同じ機能の IC を戻すことになる。

★**直流の電圧レベルでは判定できない。** 映像出力の多くは結合コンデンサで直流を
切っている(家庭用ゲーム機など)ので、75Ω 終端の後ろの平均電圧は繋がっていても
0V で、未接続と区別できない。FPGA の普通の入力ピンに直接入れても、閾値(約1.4V)に
対して同期の深さ 0.3V では切り替わらない。**見るべきは「振れているか」**。

そこで ECP5 の差動入力(LVDS 用の入力バッファ)を比較器として使う。FPGA で簡易
ADC を作るときの定番の使い方。1系統あたり抵抗3〜4本とコンデンサ1〜2個:

```
 映像線(75Ω終端の後ろ。TVP へ行く線から分岐)
   │
   ├─ 1kΩ ─┬──────────────── FPGA 差動入力 +   信号そのもの
   │       │
   │       └─ 10kΩ ─┬─────── FPGA 差動入力 −   信号の平均(基準)
   │                 │
   │               100nF
   │
   (両方を差動入力の同相範囲へ持ち上げるバイアス。抵抗分圧で 1.2V 付近)
```

- 同期パルスのたびに + が平均より約 0.3V 下がって差動入力が反転する。FPGA が
  sys ドメインで反転を数えれば key 0x2A と同じく fH が出る
- **未接続では + と − が同じ電圧に落ち着くので反転しない**(0 と数えて「信号なし」)。
  浮いたシュミット入力が自己発振する問題(v1.0 の R47-R50 の件)が起きにくい
- 1kΩ は FPGA の入力容量で 75Ω の線を乱さないための分離
- **置き場所はどちらもメイン基板。** 入力1 は FFC で届いた Y(GIN_1 / SOGIN_1 へ
  行く線)、入力2 はミニDIN8 の CSYNC(1/2分圧の前)から取る。小亀基板は変えない
  (FFC の予備線は1本しかなく、差動の2本を返せない)
- FPGA 側は key 0x2A と同じ作りのカウンタを端子ごとに足し、新しい CONFIG キーで
  返す。**数えるのは sys ドメインで**(TVP の DATACLK は選んでいる入力にロックして
  いるので、他の入力の測定には使えない)
- CSYNC は垂直帰線に等化パルスが入るので数は fH より少し多い。毎フレーム同じだけ
  多いので「2回の読みの差」の判定には影響しない

**採用前に確かめること**(いずれも未確認):

1. ECP5 の差動入力の同相範囲と、反転に要る差動電圧(閾値)。0.3V の同期で確実に
   反転するか
2. Colorlight i5 の SO-DIMM の空きピンに、**差動の組になる2本**が2系統ぶんあるか
   (下の「SO-DIMM割当(P4クラスタの空き)」から選ぶ)
3. 映像の暗い部分やノイズで余計に反転しないか。ヒステリシスが無いので、
   カウント値の安定性に頼ることになる

試し方: いまの基板の空きピンに抵抗とコンデンサを空中配線し、ゲートウェアに
カウンタを足して、コンポジット(入力1)を繋いだとき・抜いたときの値を見る。

**採らなかった案:** 小さな比較器(SOT-23-5)を1個ずつ置く案は、ヒステリシスを
付けられて確実だが IC が増える。ジャックの切り替え接点でケーブルの有無を見る案は
部品が要らないが、相手の電源が入っているかは分からない。

### ついでに直すもの(ゲートウェア)

- key 0x60(SOGOUT の水平周期)は、コンポジットを映していても 3311〜65519 と
  毎回違う値を返す。変化し続ける16bitカウンタを `MultiReg` でそのまま sys へ
  渡しているためと見ている(ビットごとに別の瞬間を拾う)。窓で確定させた値を
  渡す形にする(`gateware/retrocastx_capture.py` の `stat_sog_hlen`)

## 音声入力(4系統)

| 系統 | 経路 | 変換 |
|---|---|---|
| RGB端子音声 | J1(D-SUB15)**ピン10=L / ピン11=R** → **U13** PCM1808(直結) | 16bit/48kHz I2S |
| ミニDIN8音声 | J13 **ピン2=L / ピン1=R** → **U14** PCM1808(直結) | 16bit/48kHz I2S |
| 小亀基板音声 | J15(FFC **1=L / 3=R**)← RCA白/赤 → **U17** PCM1808 | 16bit/48kHz I2S |
| 光デジタル | J8(PLR135/T10 TOSLINK) → FPGA直結 | S/PDIFをゲートウェアでデコード |

- **クロック**: X3(12.288MHz XO =256fs@48kHz)は **FPGAにだけ**入る
  (SO-DIMM 130 = F1 = PCLKC6_1)。**ADCのSCKIはFPGAが出し直したもの**で、
  SO-DIMM 147(D2)から両ADCへ配る。BCK(143)= MCLK/4 = 3.072MHz、
  LRCK(145)= MCLK/256 = 48kHz も同じくFPGA生成の共通供給。
  **DOUTのみ個別**(U13=141, U14=139, U17=129)なのでアナログ3系統は同時キャプチャ可能。
  S/PDIFのDIRチップは不要(FPGAでデコード)

  ★**XOはADCに直接は繋がっていない。** 以前この節は「XO→両ADCのSCKIとFPGA」と
  書いていたが誤りで、音が出ない件の切り分けで探す場所を間違える原因になった
  (2026-09-03)。信号を追うときは必ず FPGA の出力(147)から見ること。

- ★**実装の注意: SCKI(6番)は DGND(5番)の真隣。** TSSOP-14 の 0.65mm ピッチなので
  5-6間がブリッジすると MCLK が GND に落ちる。**両ADCがMCLKを共有しているので、
  片方のICの下のブリッジで音声が2系統とも死ぬ。** 実際に v0.9.0 で発生した
  (2026-09-03)。そのときの症状:

  | 観測 | 値 |
  |---|---|
  | 転送される音声サンプル | 両ch**ビット単位で完全にゼロ**(入力無しならディザが出るはず) |
  | サンプルレート | 48kHz で正常(FPGA内部とBCK/LRCK生成は無事) |
  | ADC 7番(LRCK)/ 8番(BCK) | 正常に観測できる |
  | ADC 6番(SCKI) | **完全に平坦**(鈍りではない) |
  | ADC 1番(VREF) | **0V**(SCKIが無いとリセットが解けず基準電圧が立たない) |
  | アナログ5V(C60) | 正常 |

  VREF=0V は原因ではなく**結果**。この並びが出たら 5-6 間のブリッジを疑う
- **D-SUB音声の切り離しジャンパは削除した**(2026-08-11)。当初は「VGA HD-15の
  ピン4/11はID/DDCなので、一般VGAケーブルを挿す運用では切り離せるように」という
  理由で入れていたが、**コネクタを2列DA-15(X68000式)に変えた時点で3列のVGAケーブルは
  物理的に挿せなくなり**、この理由は消えていた。その後「LINE入力優先時」と読み替えられて
  いたが、**LINE入力はADCが別(U1=D-SUB / U2=LINE)でDOUTも個別**なので D-SUB 側を切る
  必要はない。よって直結にした
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
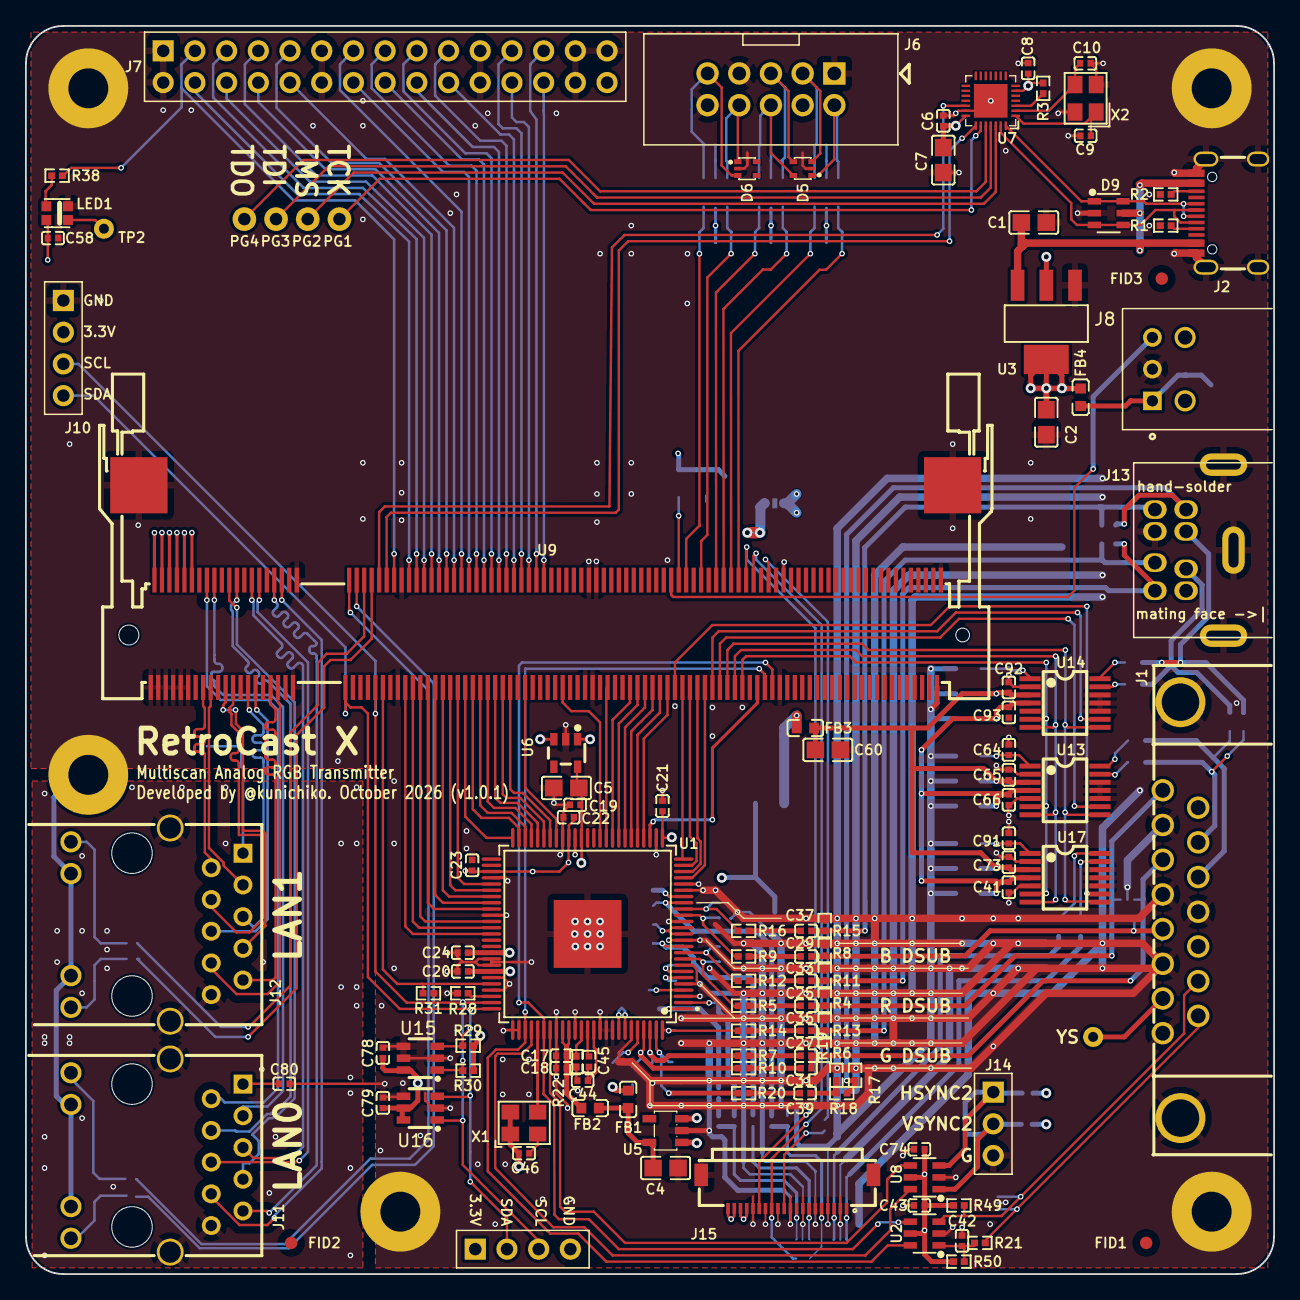
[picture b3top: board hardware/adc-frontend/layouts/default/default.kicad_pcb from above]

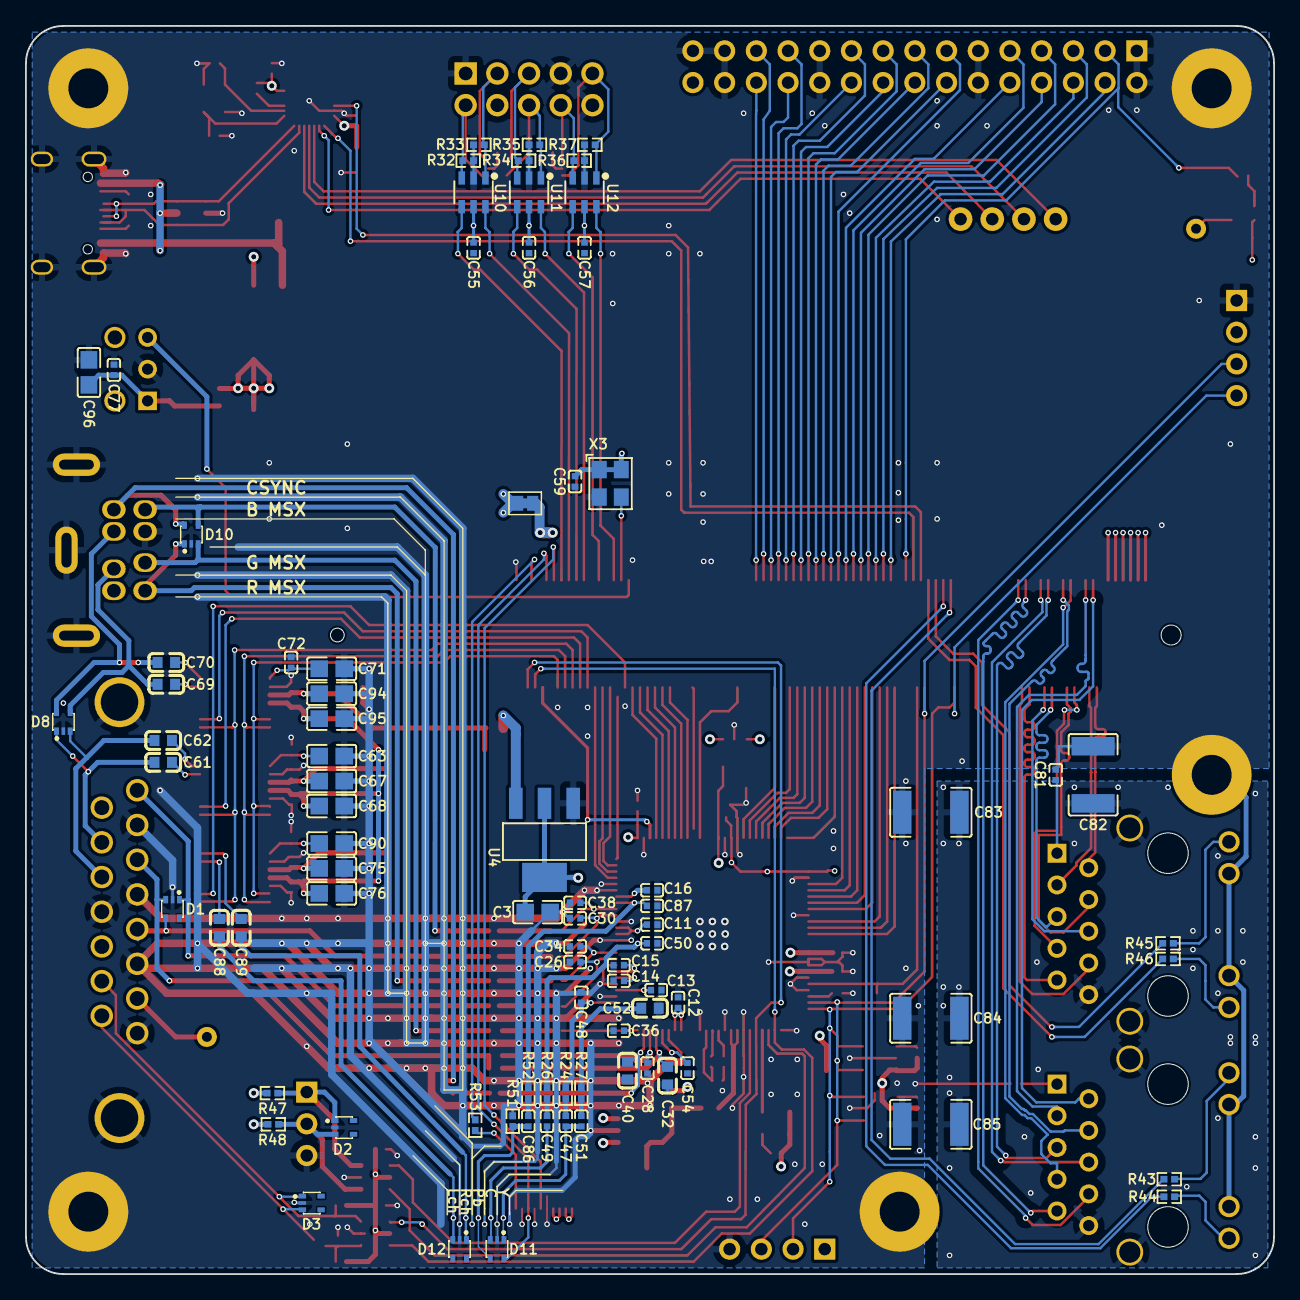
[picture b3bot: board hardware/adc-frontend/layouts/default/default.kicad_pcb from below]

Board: 4 copper layers, 100.0 x 100.0 mm, 204 parts (82 on the bottom side), 196 nets.

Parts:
C1, C2, C3, C4, C5, C7, C60, C63, C67, C68, C71, C75, C76, C90, C94, C95, C96: 10µF ±10%; C0805
C6, C8, C11, C12, C13, C14, C15, C16, C17, C18, C19, C20, C21, C22, C23, C24, C25, C27, C29, C31, C33, C35, C37, C39, C41, C43, C44, C46, C47, C49, C55, C56, C57, C58, C59, C64, C65, C66, C72, C73, C74, C77, C78, C79, C80, C81, C86, C91, C92, C93: 100nF ±10%; C0402
C9, C10: 22pF ±5%; C0402
C26, C28, C30, C34, C36, C38, C48, C50, C87: 33pF ±5%; C0402
C32, C40, C52: 33pF ±5%; C0603_DNP
C42, C51: 1nF ±10%; C0402
C45: 4.7nF ±10%; C0402
C54: 10nF ±10%; C0402
C61, C62, C69, C70, C88, C89: 1µF ±10%; C0603
C82, C83, C84, C85: 4.7nF ±10%; C1812
D1, D2, D3, D5, D6, D8, D10, D11, D12: EMT6_L1.6-W1.2-P0.50-LS1.6-BL
D9: SOT-23-6_L2.9-W1.6-P0.95-LS2.8-BL
FB1, FB2, FB3, FB4: L0603
FID1, FID2, FID3: Fiducial_1mm_Mask2mm
H1, H2, H3, H4, H5: MountingHole_3.2mm_M3_Pad
J1: DSUB-TH_DS1037-15FNAKT74-0CC
J2: USB-C_SMD-TYPE-C-31-M-12_1
J6: IDC-TH_10P-P2.54-V-R2-C5-S2.54
J7: Header_2x15_P2.54mm
J8: PLR135_T10
J9, J10: Header_1x4_P2.54mm
J11, J12: RJ45-TH_HR911130A
J13: MJ373_8B
J14: Header_1x3_P2.54mm
J15: FPC-SMD_20P-P0.50_HDGC_0.5K-1.5-20PWB
JP1: SolderJumper_2_Bridged
LED1: LED-SMD_4P-L2.2-W2.0-P1.00_WS2815C-2020-4P
PG1, PG2, PG3, PG4: PogoPin_D1.0mm
R1, R2: 5.1kΩ ±1%; R0402
R3, R32, R33, R34, R35, R36, R37, R47, R48, R49, R50: 10kΩ ±1%; R0402
R4, R6, R8, R11, R13, R15, R17, R51: 75Ω ±1%; R0402
R5, R7, R9, R10, R12, R14, R16, R20, R21, R24, R26, R27, R38, R43, R44, R45, R46, R52, R53: 220Ω ±1%; R0402
R18, R19, R22: 1.5kΩ ±1%; R0402
R28, R29, R30, R31: 2.2kΩ ±1%; R0402
TP1, TP2: TestPoint_TH1
U1: HTQFP-100_L14.0-W14.0-P0.50-LS16.0-BL-EP6.2
U2, U8, U10, U11, U12: SOT-23-6_L2.9-W1.6-P0.95-LS2.8-BL
U3, U4: SOT-223-3_L6.5-W3.4-P2.30-LS7.0-BR
U5: SOT-23-5_L3.0-W1.7-P0.95-LS2.8-BR
U6: SOT-23-5_L2.9-W1.6-P0.95-LS2.8-BR
U7: QFN-28_L4.0-W4.0-P0.40-BL-EP2.7
U9: SO-DIMM-SMD_200P-P0.60_1473005-4
U13, U14, U17: TSSOP-14_L5.0-W4.4-P0.65-LS6.4-BL
U15, U16: SOT-23-6_L2.9-W1.6-P0.95-LS2.8-BR
X1, X3: OSC-SMD_4P-L3.2-W2.5-BL
X2: CRYSTAL-SMD_4P-L3.2-W2.5-BL

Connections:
154: R53.1, U9.154
A5: J2.A5, R1.1
B5: J2.B5, R2.1
aud_din8_l: C69.1, D8.4, J13.2
aud_din8_l_ac: C69.2, U14.13
aud_din8_r: C70.1, D8.5, J13.1
aud_din8_r_ac: C70.2, U14.14
aud_dsub_l: C61.1, D8.1, J1.10
aud_dsub_l_ac: C61.2, U13.13
aud_dsub_r: C62.1, D8.3, J1.11
aud_dsub_r_ac: C62.2, U13.14
aud_kokame_l: C88.1, D12.3, J15.1
aud_kokame_l_ac: C88.2, U17.13
aud_kokame_r: C89.1, D12.1, J15.3
aud_kokame_r_ac: C89.2, U17.14
aud_vref_din8: C71.1, C72.1, U14.1
aud_vref_dsub: C63.1, C64.1, U13.1
aud_vref_kokame: C90.1, C91.1, U17.1
audio_mclk_in: U9.130, X3.3
avdd: C13.1, C14.1, C15.1, C16.1, FB1.2, U1.4, U1.6, U1.7, U1.19
bck: U9.143, U13.8, U14.8, U17.8
bin1: C87.1, R52.2, U1.18
bin2: C38.1, R16.2, U1.17
bin3: C30.1, R9.2, U1.16
chassis: C82.1, C83.1, C84.1, C85.1, J11.P10, J11.SHIELD0, J11.SHIELD1, J12.P10, J12.SHIELD0, J12.SHIELD1
dataclk: U1.28, U9.151
dbg01_m1: J7.3, R38.1, U9.54
dbg02_n2: J7.4, U9.58
dbg03_n3: J7.5, U9.60
dbg04_t2: J7.6, U9.62
dbg05_m3: J7.7, U9.64
dbg06_t3: J7.8, U9.66
dbg07_r3: J7.9, U9.68
dbg08_n4: J7.10, U9.70
dbg09_m4: J7.13, U9.72
dbg10_l4: J7.14, U9.74
dbg11_l5: J7.15, U9.76
dbg12_p16: J7.16, U9.78
dbg13_j16: J7.17, U9.80
dbg14_j18_pclk: J7.18, U9.82
dbg15_j17: J7.19, U9.84
dbg16_h18: J7.20, U9.86
dbg17_h17: J7.23, U9.88
dbg18_g18: J7.24, U9.90
dbg19_h16: J7.25, U9.92
dbg20_f18: J7.26, U9.94
dn: D9.3, D9.4, J2.A7, J2.B7, U7.27
dp: D9.1, D9.6, J2.A6, J2.B6, U7.28
drgb_b: U9.142, U11.4
drgb_g: U9.144, U10.6
drgb_hs: U9.136, U12.4
drgb_i: U9.140, U11.6
drgb_r: U9.146, U10.4
drgb_vs: U9.132, U12.6
drgbi_b: D5.4, J6.5, R34.1, U11.3
drgbi_g: D5.3, J6.3, R33.1, U10.1
drgbi_hs: D6.1, J6.8, R36.1, U12.3
drgbi_i: D5.5, J6.6, R35.1, U11.1
drgbi_r: D5.1, J6.2, R32.1, U10.3
drgbi_vs: D6.3, J6.9, R37.1, U12.1
eth1_1_N: J12.P3, U9.17
eth1_1_P: J12.P2, U9.15
eth1_2_N: J12.P7, U9.21
eth1_2_P: J12.P4, U9.23
eth1_3_N: J12.P6, U9.29
eth1_3_P: J12.P5, U9.27
eth1_4_N: J12.P9, U9.33
eth1_4_P: J12.P8, U9.35
eth1_ct: C81.1, J12.P1
eth1_led_g_anode: J12.11, R45.2
eth1_led_g_gpio: R45.1, U9.46
eth1_led_y_anode: J12.14, R46.2
eth1_led_y_gpio: R46.1, U9.48
eth2_1_N: J11.P3, U9.18
eth2_1_P: J11.P2, U9.16
eth2_2_N: J11.P7, U9.22
eth2_2_P: J11.P4, U9.24
eth2_3_N: J11.P6, U9.30
eth2_3_P: J11.P5, U9.28
eth2_4_N: J11.P9, U9.34
eth2_4_P: J11.P8, U9.36
eth2_ct: C80.1, J11.P1
eth2_led_g_anode: J11.11, R43.2
eth2_led_g_gpio: R43.1, U9.42
eth2_led_y_anode: J11.14, R44.2
eth2_led_y_gpio: R44.1, U9.44
ext_clk: U1.80, X1.3
fidout: U1.22, U9.137
ft_osci: C9.1, U7.1, X2.1
ft_osco: C10.1, U7.2, X2.3
gin1: C48.1, R24.2, U1.2
gin2: C36.1, R14.2, U1.100
gin3: C28.1, R7.2, U1.98
gin4_nc: C54.1, U1.96
gnd: C1.2, C2.2, C3.2, C4.2, C5.2, C6.2, C7.2, C8.2, C9.2, C10.2, C11.2, C12.2, C13.2, C14.2, C15.2, C16.2, C17.2, C18.2, C19.2, C20.2, C21.2, C22.2, C23.2, C24.2, C26.2, C28.2, C30.2, C32.2, C34.2, C36.2, C38.2, C40.2, C41.2, C42.2, C43.2, C46.2, C48.2, C50.2, C52.2, C54.2, C55.2, C56.2, C57.2, C58.2, C59.2, C60.2, C63.2, C64.2, C65.2, C66.2, C67.2, C68.2, C71.2, C72.2, C73.2, C74.2, C75.2, C76.2, C77.2, C78.2, C79.2, C80.2, C81.2, C82.2, C83.2, C84.2, C85.2, C87.2, C90.2, C91.2, C92.2, C93.2, C94.2, C95.2, C96.2, D1.2, D2.2, D3.2, D5.2, D6.2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
hsout: U1.24, U9.133
hsync: D3.1, J1.14, R49.1, U2.3
hsync_a: U1.81, U2.4, U9.155
hsync_b: U1.82, U8.4
i2ca: R28.1, U1.73
i2s_dout_din8: U9.139, U14.9
i2s_dout_dsub: U9.141, U13.9
i2s_dout_kokame: U9.129, U17.9
jtag_tck: PG1.1, U7.23
jtag_tdi: PG3.1, U7.25
jtag_tdo: PG4.1, U7.24
jtag_tms: PG2.1, U7.26
kokame_gpio2: D11.5, J15.13, U9.150
kokame_led_din: J15.11, R53.2
kokame_sw_sel: J15.15, U9.148
led_din: LED1.3, R38.2
led_dout: LED1.1, TP2.1
lrc: U9.145, U13.7, U14.7, U17.7
nRST: R3.1, U7.3
p1v9_a: C4.1, FB1.1, FB2.1, U5.5
p1v9_d: C5.1, C19.1, C20.1, U1.39, U1.69, U6.5
p3v3_a: C3.1, C11.1, C12.1, U1.13, U1.14, U1.93, U1.94, U4.2, U4.4, U5.1, U5.3
p3v3_io: C2.1, C6.1, C7.1, C8.1, C21.1, C22.1, C23.1, C24.1, C41.1, C43.1, C46.1, C55.1, C56.1, C57.1, C58.1, C59.1, C66.1, C68.1, C74.1, C76.1, C78.1, C79.1, C93.1, C95.1, FB4.1, J7.30, J9.1, J10.2, J15.17, J15.18, LED1.4, R3.2, R29.2, R30.2, R47.2, R48.2, R49.2, R50.2, U1.26, U1.41, U1.53, U1.66, U2.5, U3.2, U3.4, U6.1, U6.3, U7.6, U7.21, U8.5, U10.5, U11.5, U12.5, U13.4, U14.4, U15.6, U16.5, U16.6, U17.4, X1.1, X1.4, X3.1, X3.4
p3v3_spdif: C77.1, C96.1, FB4.2, J8.1
p5v: C1.1, D9.5, FB3.1, J2.A4B9, J2.B4A9, J15.19, J15.20, JP1.2, U3.3, U4.3
p5v_audio: C60.1, C65.1, C67.1, C73.1, C75.1, C92.1, C94.1, FB3.2, U13.3, U14.3, U17.3
p5v_ext: JP1.1, U9.2, U9.4, U9.6, U9.8, U9.10, U9.12
pll_avdd: C17.1, C18.1, FB2.2, U1.84, U1.85
pll_f: C44.2, C45.2, U1.89
pll_filt1: R22.1, U1.87
pll_filt2: C45.1, U1.88
pll_filt_mid: C44.1, R22.2
resetb: R31.1, U1.71, U9.51
rin1: C50.1, R26.2, U1.11
rin2: C34.1, R12.2, U1.10
rin3: C26.1, R5.2, U1.9
scki: U9.147, U13.6, U14.6, U17.6
scl: J9.3, J10.3, R30.1, U1.74, U9.49, U15.1, U16.1
sda: J9.2, J10.4, R29.1, U1.75, U9.41, U15.3, U16.3
sogin1: C52.1, R27.2, U1.1
sogin2: C40.1, R20.2, U1.99
sogin3: C32.1, R10.2, U1.97
sogout: U1.25, U9.131
spdif: J8.3, U9.128
uart_rxd: U7.22, U9.52
uart_txd: U7.19, U9.50
vd_b2: U1.36, U9.99
vd_b3: U1.35, U9.111
vd_b4: U1.34, U9.117
vd_b5: U1.33, U9.119
vd_b6: U1.32, U9.121
vd_b7: U1.31, U9.123
vd_b8: U1.30, U9.125
vd_b9: U1.29, U9.127
vd_g2: U1.50, U9.73
vd_g3: U1.49, U9.75
vd_g4: U1.48, U9.77
vd_g5: U1.47, U9.79
vd_g6: U1.46, U9.81
vd_g7: U1.45, U9.83
vd_g8: U1.44, U9.85
vd_g9: U1.43, U9.89
vd_r2: U1.63, U9.57
vd_r3: U1.62, U9.59
vd_r4: U1.61, U9.61
vd_r5: U1.59, U9.63
vd_r6: U1.58, U9.65
vd_r7: U1.57, U9.67
vd_r8: U1.56, U9.69
vd_r9: U1.55, U9.71
vin_b2: C37.1, D10.4, J13.6, R15.1
vin_b2_ac: C37.2, R16.1
vin_b3: C29.1, D1.4, J1.5, R8.1
vin_b3_ac: C29.2, R9.1
vin_c1: C49.1, D11.3, J15.7
vin_c1_ac: C49.2, R26.1
vin_csync2: D10.5, J13.3, R17.1, R18.1
vin_csync2_ac: C39.2, R20.1
vin_csync2_div: C39.1, R18.2, R19.1
vin_g2: C35.1, D10.3, J13.7, R13.1
vin_g2_ac: C35.2, R14.1
vin_g3: C27.1, C31.1, D1.3, J1.3, R6.1
vin_g3_ac: C27.2, R7.1
vin_g3_sog_ac: C31.2, R10.1
vin_hsync2: D2.1, J14.1, R47.1, U8.3
vin_pb1: C86.1, D11.4, J15.5, R51.1
vin_pb1_ac: C86.2, R52.1
vin_r2: C33.1, D10.1, J13.8, R11.1
vin_r2_ac: C33.2, R12.1
vin_r3: C25.1, D1.1, J1.1, R4.1
vin_r3_ac: C25.2, R5.1
vin_vsync2: D2.3, J14.2, R48.1, U8.1
vin_y1: C47.1, C51.1, D11.1, J15.9
vin_y1_ac: C47.2, R24.1
vin_y1_sog_ac: C51.2, R27.1
vsout: U1.23, U9.135
vsync: D3.3, J1.15, R21.1
vsync_a: U1.78, U2.6, U9.153
vsync_b: U1.79, U8.6
vsync_delayed: C42.1, R21.2, R50.1, U2.1
ys: J1.7, TP1.1

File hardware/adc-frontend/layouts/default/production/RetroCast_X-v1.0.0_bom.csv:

Designator,Footprint,Quantity,Value,LCSC Part #
"C1, C2, C3, C4, C5, C60, C63, C67, C68, C7, C71, C75, C76, C90, C94, C95, C96",C0805,17,10µF ±10%,C15850
"C10, C9",C0402,2,22pF ±5%,C70464
"C11, C12, C13, C14, C15, C16, C17, C18, C19, C20, C21, C22, C23, C24, C25, C27, C29, C31, C33, C35, C37, C39, C41, C43, C44, C46, C47, C49, C51, C55, C56, C57, C58, C59, C6, C64, C65, C66, C72, C73, C74, C77, C78, C79, C8, C80, C81, C86, C91, C92, C93",C0402,51,100nF ±10%,C1525
"C26, C28, C30, C34, C36, C38, C48, C50, C87",C0402,9,33pF ±5%,C70465
"C32, C40, C52",C0402,3,33pF ±5%,
C42,C0402,1,1nF ±10%,C1523
C45,C0402,1,4.7nF ±10%,C1538
C54,C0402,1,10nF ±10%,C15195
"C61, C62, C69, C70, C88, C89",C0603,6,1µF ±10%,C15849
"C82, C83, C84, C85",C1812,4,4.7nF ±10%,C309511
"D1, D10, D11, D12, D2, D3, D5, D6, D8",EMT6_L1.6-W1.2-P0.50-LS1.6-BL,9,,C895163
D9,SOT-23-6_L2.9-W1.6-P0.95-LS2.8-BL,1,,C7519
"FB1, FB2, FB3, FB4",L0603,4,,C76815
J1,DSUB-TH_DS1037-15FNAKT74-0CC,1,,C77836
"J10, J9",Header_1x4_P2.54mm,2,,
"J11, J12",RJ45-TH_HR911130A,2,,C54408
J13,MJ373_8B,1,,
J14,Header_1x3_P2.54mm,1,,
J15,FPC-SMD_20P-P0.50_HDGC_0.5K-1.5-20PWB,1,,C2919559
J2,USB-C_SMD-TYPE-C-31-M-12_1,1,,C165948
J6,IDC-TH_10P-P2.54-V-R2-C5-S2.54,1,,C492442
J7,Header_2x15_P2.54mm,1,,
J8,PLR135_T10,1,,
LED1,LED-SMD_4P-L2.2-W2.0-P1.00_WS2815C-2020-4P,1,,C52917434
"PG1, PG2, PG3, PG4",PogoPin_D1.0mm,4,,
"R1, R2",R0402,2,5.1kΩ ±1%,C25905
"R10, R12, R14, R16, R20, R21, R24, R26, R27, R38, R43, R44, R45, R46, R5, R52, R53, R7, R9",R0402,19,220Ω ±1%,C25091
"R11, R13, R15, R17, R4, R51, R6, R8",R0402,8,75Ω ±1%,C25133
"R18, R19, R22",R0402,3,1.5kΩ ±1%,C25867
"R28, R29, R30, R31",R0402,4,2.2kΩ ±1%,C25879
"R3, R32, R33, R34, R35, R36, R37, R47, R48, R49, R50",R0402,11,10kΩ ±1%,C25744
"TP1, TP2",TestPoint_TH1,2,,
U1,HTQFP-100_L14.0-W14.0-P0.50-LS16.0-BL-EP6.2,1,,C3824085
"U10, U11, U12, U2, U8",SOT-23-6_L2.9-W1.6-P0.95-LS2.8-BL,5,,C10429
"U13, U14, U17",TSSOP-14_L5.0-W4.4-P0.65-LS6.4-BL,3,,C55513
"U15, U16",SOIC-8_L4.9-W3.9-P1.27-LS6.0-BL,2,,C46840
"U3, U4",SOT-223-3_L6.5-W3.4-P2.30-LS7.0-BR,2,,C92517
U5,SOT-23-5_L3.0-W1.7-P0.95-LS2.8-BR,1,,C59969
U6,SOT-23-5_L2.9-W1.6-P0.95-LS2.8-BR,1,,C2862411
U7,QFN-28_L4.0-W4.0-P0.40-BL-EP2.7,1,,C18221627
U9,SO-DIMM-SMD_200P-P0.60_1473005-4,1,,C428482
X1,OSC-SMD_4P-L3.2-W2.5-BL,1,,C725995
X2,CRYSTAL-SMD_4P-L3.2-W2.5-BL,1,,C2682774
X3,OSC-SMD_4P-L3.2-W2.5-BL,1,,C20617595
